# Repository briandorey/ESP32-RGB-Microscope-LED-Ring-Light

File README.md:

# ESP32 RGB Microscope LED Ring Light
ESP32 based RGB LED controller and LED ring for a microscope

The **PCB files** are in Diptrace format.

The **firmware** folder contains the firmware for the ESP32 module

The **3D Models** folder contains design files for the plastic case.

More details about this project are on my blog at [https://www.briandorey.com/post/esp32-rgb-led-microscope-ringlight](https://www.briandorey.com/post/esp32-rgb-led-microscope-ringlight)

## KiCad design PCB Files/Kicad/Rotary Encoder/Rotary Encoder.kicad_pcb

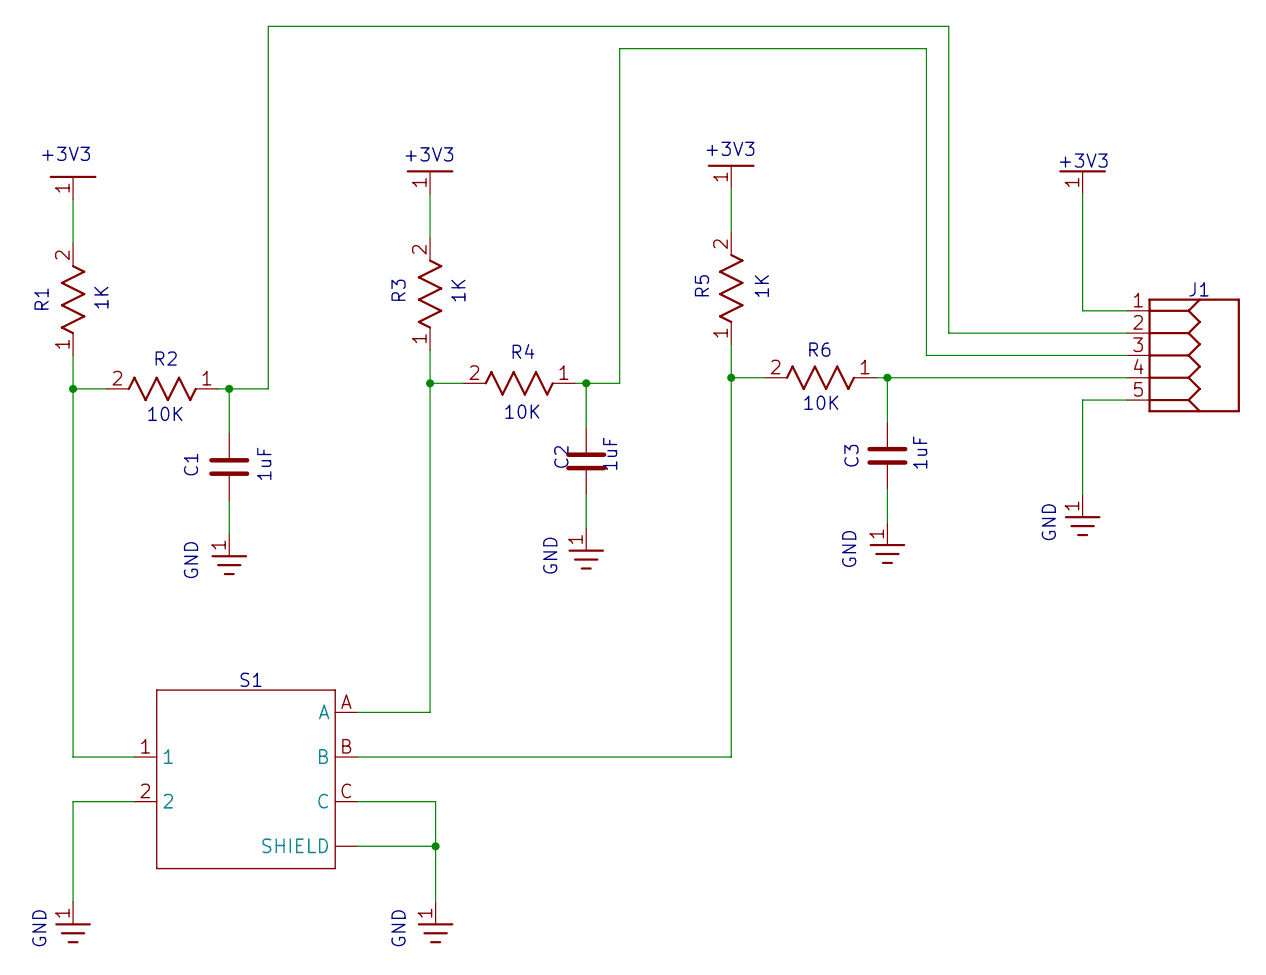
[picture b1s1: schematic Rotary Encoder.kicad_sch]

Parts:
C1, C2, C3: 1uF; CAP_0603
J1: DEV_J1; RHDRV5W80P254_5X1_1320X250H875_AP1
R1, R3, R5: 1K; RES_0603
R2, R4, R6: 10K; RES_0603
S1: 482020514001; SW_482020514001

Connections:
3V3: J1.1, R1.2, R3.2, R5.2
A: C2.1, J1.3, R4.1
B: C3.1, J1.4, R6.1
GND: C1.2, C2.2, C3.2, J1.5, S1.2, S1.C, S1.S1 (SHIELD), S1.S2 (SHIELD)
Net_1: R1.1, R2.2, S1.1
Net_5: R3.1, R4.2, S1.A
Net_7: R5.1, R6.2, S1.B
SW: C1.1, J1.2, R2.1

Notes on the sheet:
GND
+3V3
1uF
10K

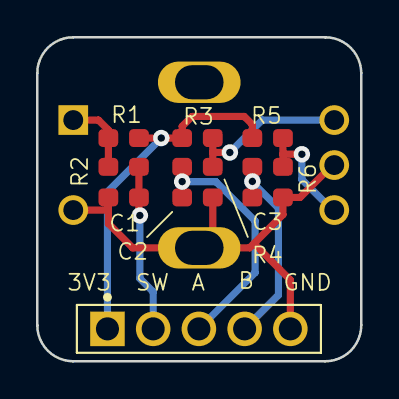
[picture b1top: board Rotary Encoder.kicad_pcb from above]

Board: 2 copper layers, 18.0 x 18.0 mm, 11 parts (1 on the bottom side), 8 nets.

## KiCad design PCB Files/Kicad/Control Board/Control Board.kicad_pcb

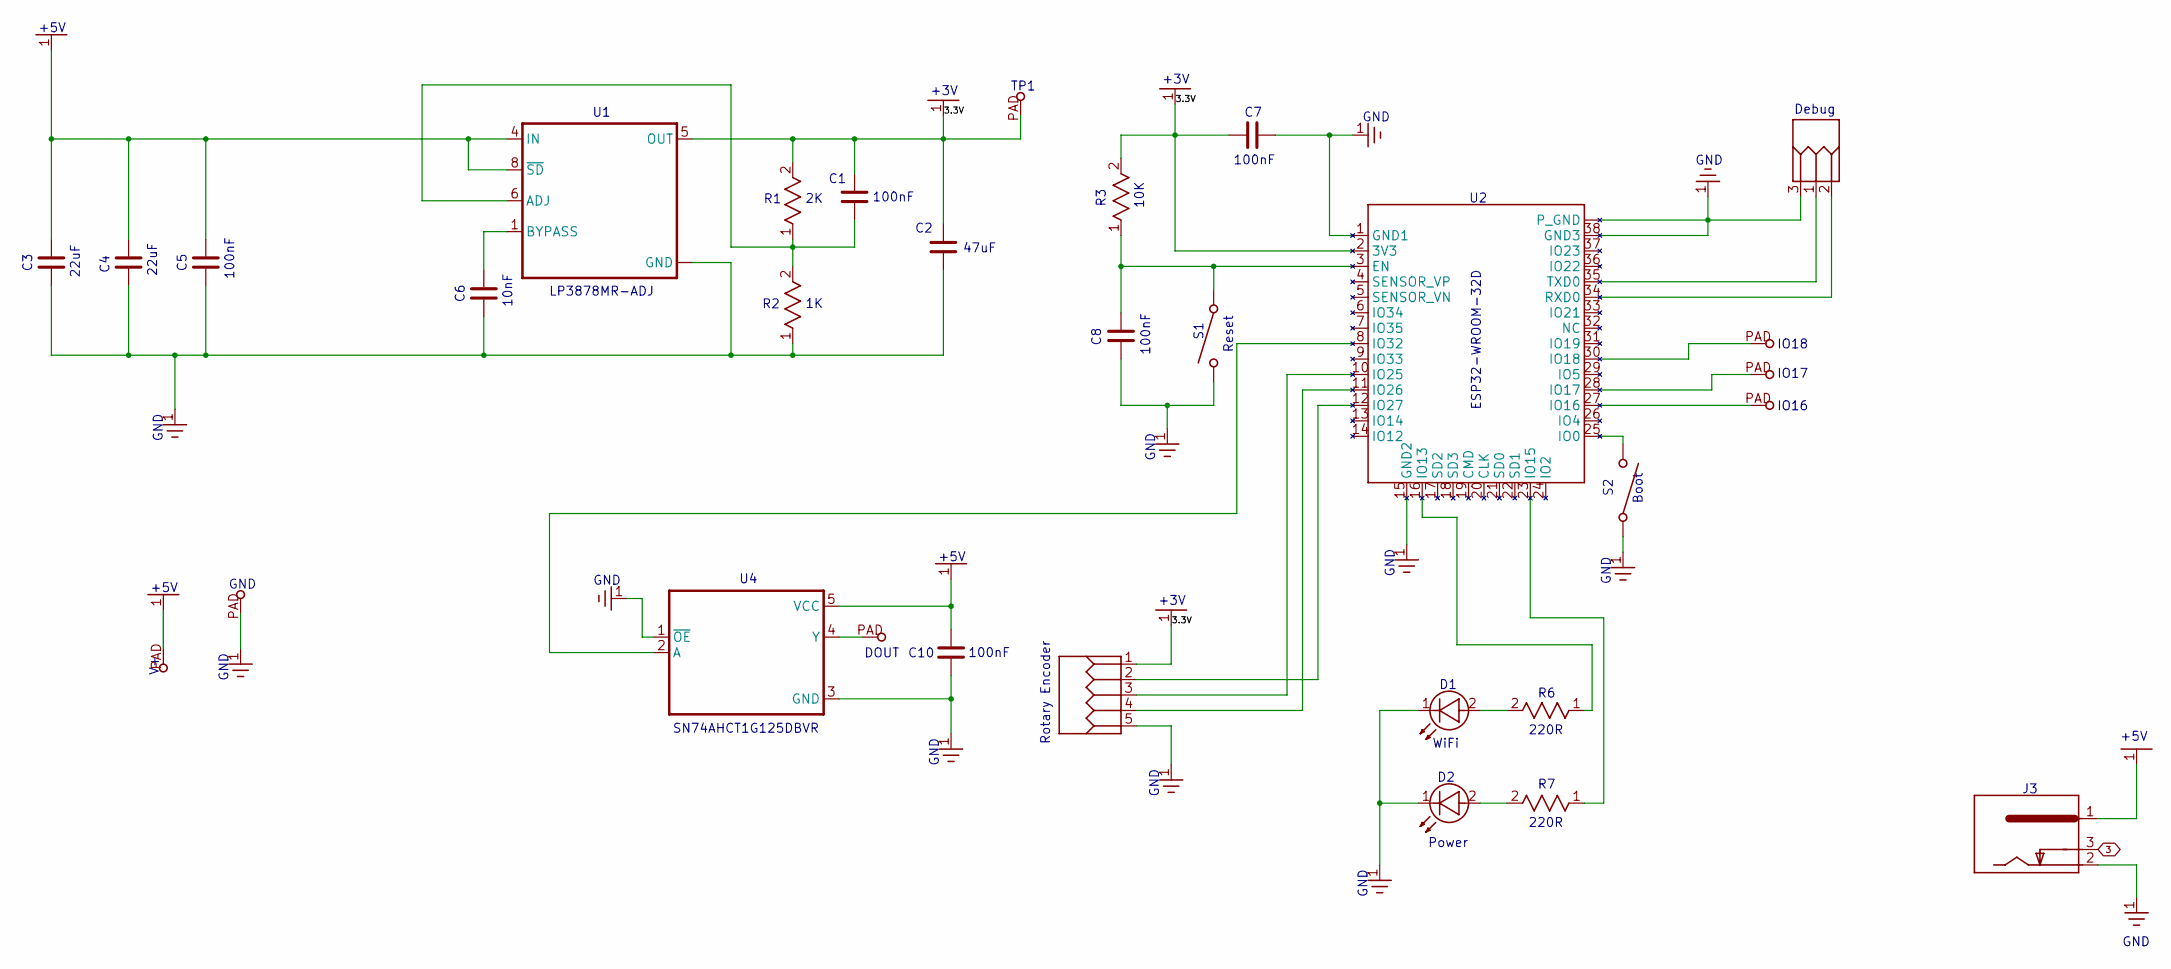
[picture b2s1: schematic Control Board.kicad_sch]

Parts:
C1, C5, C7, C8, C10: 100nF; CAP_0603_M
C2: 47uF; CAP_1210_M
C3, C4: 22uF; CAP_1210_M
C6: 10nF; CAP_0603_M
D1: WiFi; DIO_0805
D2: Power; DIO_0805
DOUT0: SMD/RREC2.0X4.0; LEAD_1.00MM
GND0: SMD/RREC2.0X4.0; LEAD_1.00MM
IO16, IO17, IO18: SMD/RREC2.0X4.0; LEAD_1.00MM
J1: DEBUG; TEST_PADS_3_PIN
J2: ROTARY_ENCODER; RHDRV5W80P254_5X1_1320X250H875_AP1
J3: 694108301002; CUI_PJ-035DH
R1: 2K; RES_0603
R2: 1K; RES_0603
R3: 10K; RES_0603
R6, R7: 220R; RES_0603_19
S1: RESET; EVQPT9A15
S2: BOOT; EVQPT9A15
TP1: 3V3; SMD_R1.3X1.3
U1: LP3878MR-ADJ; SOIC-8EP_150MIL
U2: ESP32-WROOM-32D
U4: SN74AHCT1G125DBVR; SOT95P280X145-5N
V+0: SMD/RREC2.0X4.0; LEAD_1.00MM

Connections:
3.3V: C1.1, C2.1, C7.1, J2.1, R1.2, R3.2, TP1.PAD, U1.5 (OUT), U2.2 (3V3)
5V: C3.1, C4.1, C5.1, C10.1, J3.1, U1.4 (IN), U1.8 (~SD), U4.5 (VCC), V+0.PAD
GND: C2.2, C3.2, C4.2, C5.2, C6.2, C7.2, C8.2, C10.2, D1.1 (K), D2.1 (K), GND0.PAD, J1.3 (1), J2.5, J3.2, R2.1, S1.2 (C2), S1.3 (C2), S2.1 (C1), S2.4 (C1), U1.3 (GND), U1.9 (GND), U2.1 (GND1), U2.15 (GND2), U2.38 (GND3), U2.39 (P_GND), U2.40, U2.41, U2.42 (P_GND), U2.43 (P_GND), U2.44, U2.45, U2.46, U2.47, U4.1 (~OE), U4.3 (GND); also elsewhere on the board
Net_0: U2.8 (IO32), U4.2 (A)
Net_1: R7.1 (A), U2.23 (IO15)
Net_2: J2.4, U2.11 (IO26)
Net_3: IO16.PAD, U2.27 (IO16)
Net_6: S2.2 (C2), S2.3 (C2), U2.25 (IO0)
Net_7: J2.3, U2.10 (IO25)
Net_8: C8.1, R3.1, S1.1 (C1), S1.4 (C1), U2.3 (EN)
Net_10: DOUT0.PAD, U4.4 (Y)
Net_11: R6.1 (A), U2.16 (IO13)
Net_12: J2.2, U2.12 (IO27)
Net_13: D1.2 (A), R6.2 (B)
Net_14: D2.2 (A), R7.2 (B)
Net_18: C6.1, U1.1 (BYPASS)
Net_19: C1.2, R1.1, R2.2, U1.6 (ADJ)
Net_20: IO17.PAD, U2.28 (IO17)
Net_21: IO18.PAD, U2.30 (IO18)
RX: J1.2 (3), U2.34 (RXD0)
TX: J1.1 (2), U2.35 (TXD0)

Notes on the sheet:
+5V
GND
+3V
100nF
Boot
47uF
Debug
IO17
10nF
22uF
220R
Reset
Power
10K
IO16
SN74AHCT1G125DBVR
WiFi
DOUT
LP3878MR-ADJ
Rotary Encoder
C10
IO18
TP1
ESP32-WROOM-32D

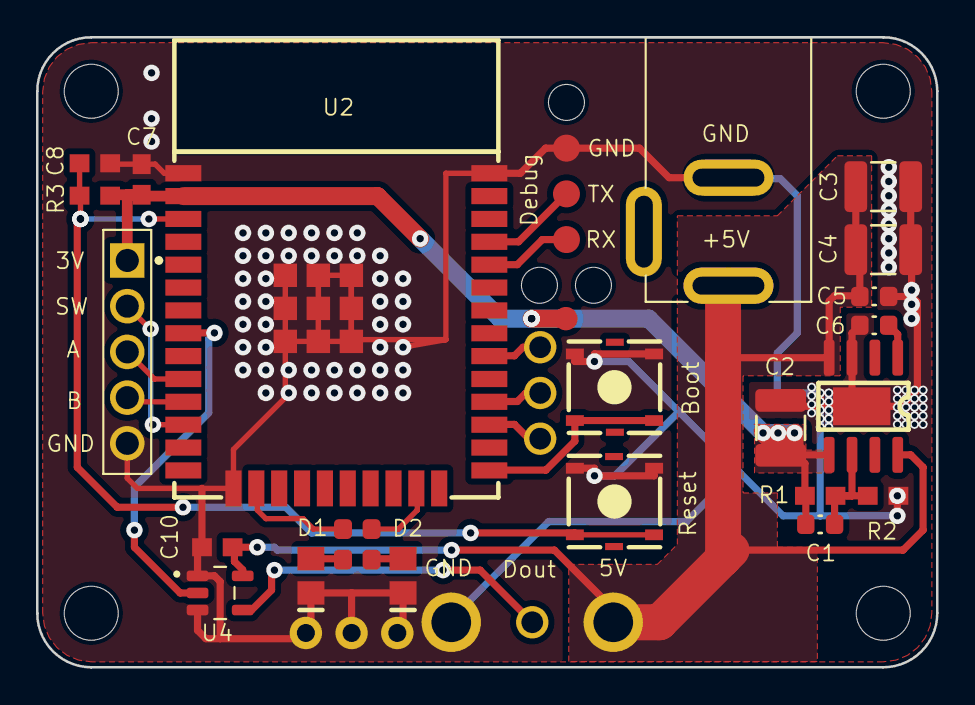
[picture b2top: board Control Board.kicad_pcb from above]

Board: 2 copper layers, 50.0 x 35.0 mm, 38 parts (0 on the bottom side), 21 nets.

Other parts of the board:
Pad1, Pad2, Pad3: PAD; Pad
UNK_HOLE_0: dummyfp0
UNK_HOLE_1: dummyfp1
UNK_HOLE_2: dummyfp2
UNK_HOLE_3: dummyfp3

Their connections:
GND: Pad1.1, Pad2.1, Pad3.1; also elsewhere on the board

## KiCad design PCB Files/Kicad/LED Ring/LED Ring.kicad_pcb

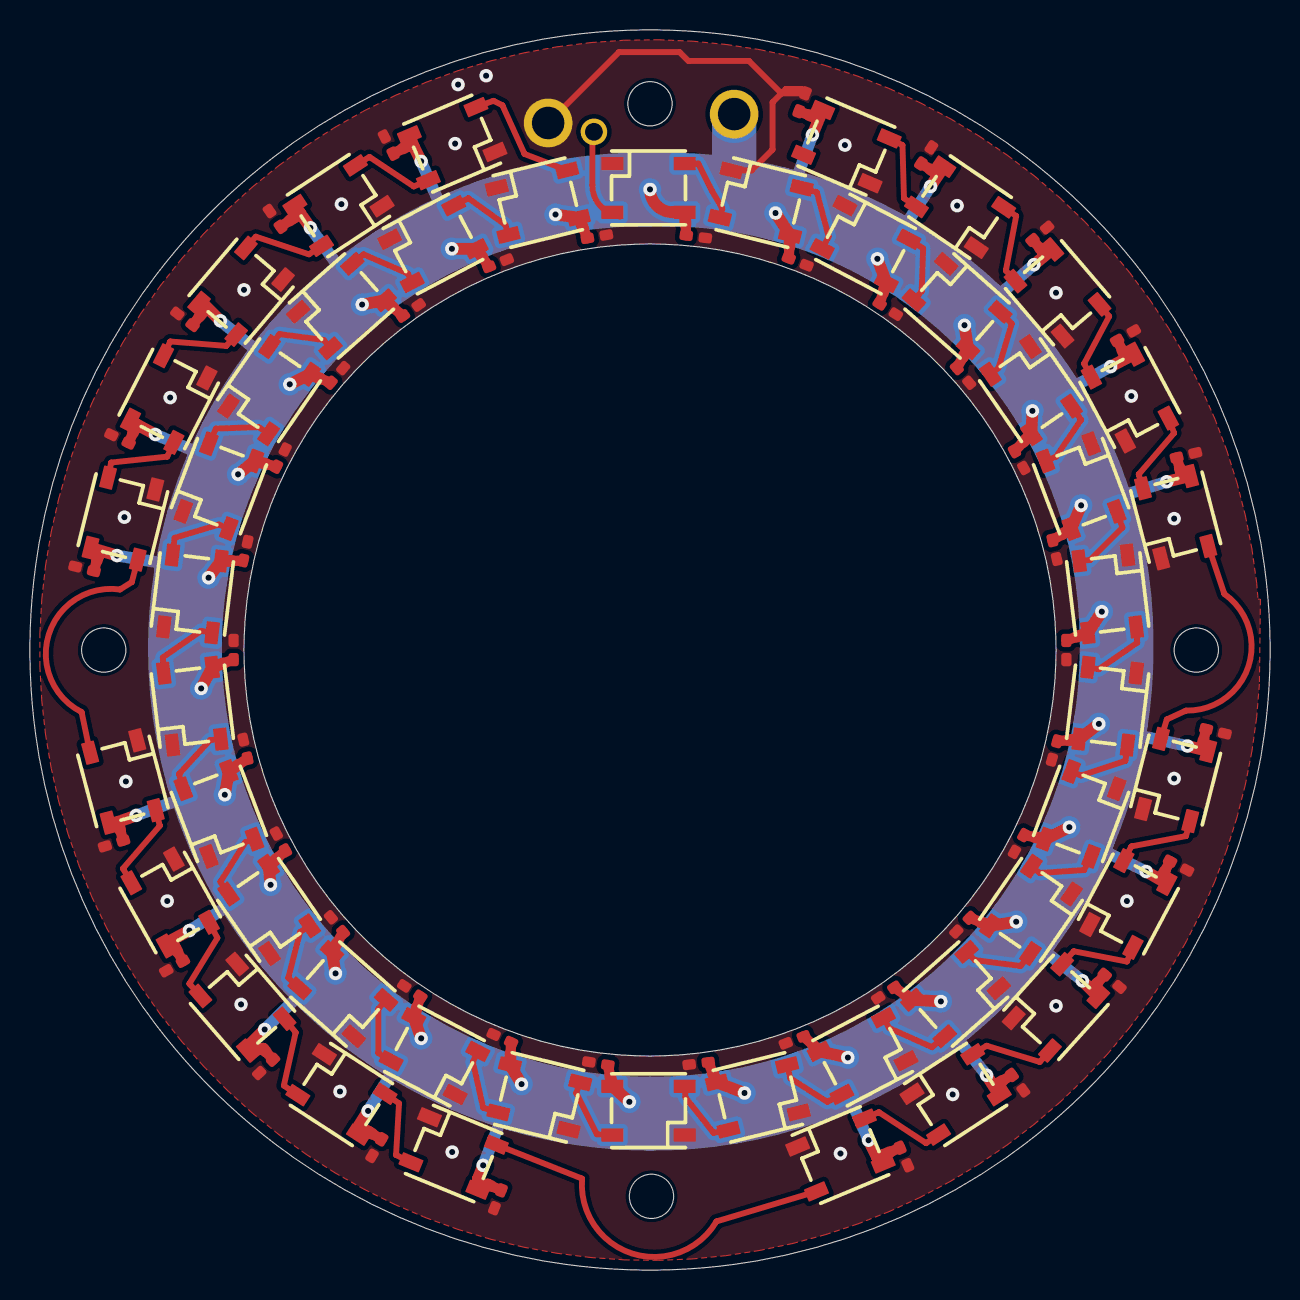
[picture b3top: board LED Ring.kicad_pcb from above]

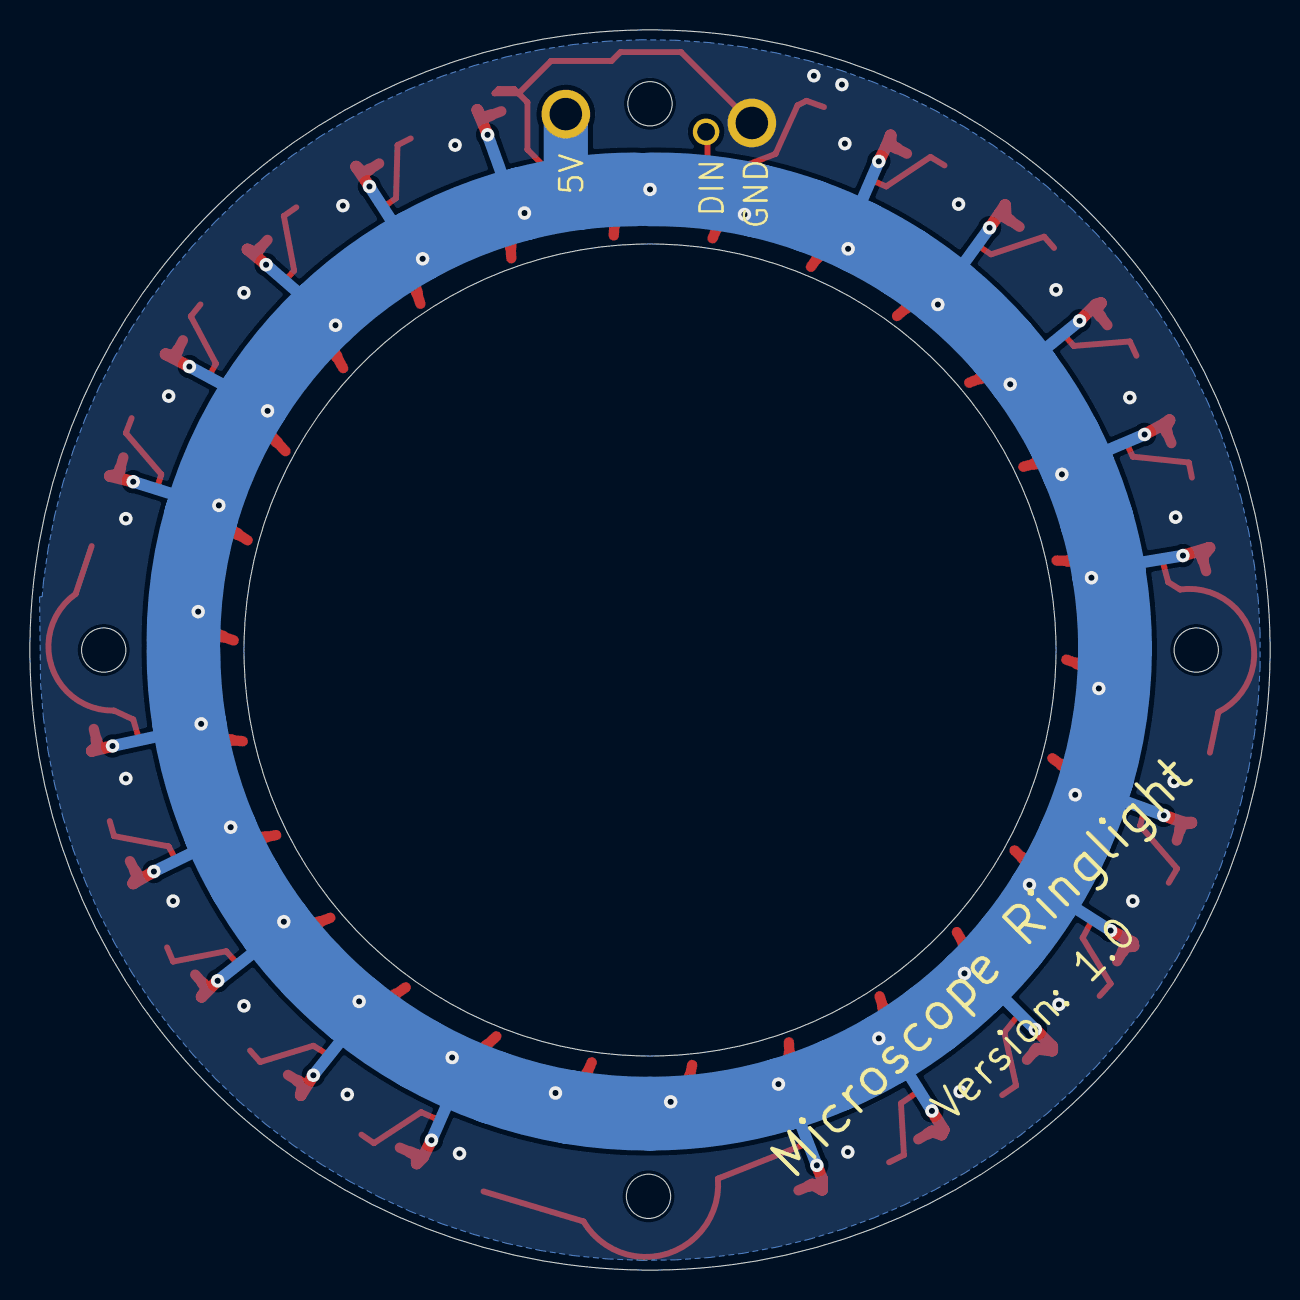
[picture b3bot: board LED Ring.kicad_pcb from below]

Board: 2 copper layers, 84.0 x 84.0 mm, 99 parts (3 on the bottom side), 48 nets.

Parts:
C1, C2, C3, C4, C5, C6, C7, C8, C9, C10, C11, C12, C13, C14, C15, C16, C17, C18, C19, C20, C21, C22, C23, C24, C25, C26, C27, C28, C29, C30, C31, C32, C33, C34, C35, C36, C37, C38, C39, C40, C41, C42, C43, C44, C45, C46: CAP_0603; CAP_0402
DIN0: SMD/RREC2.0X4.0; Lead_1.00mm
GND0: SMD/RREC2.0X4.0; Lead_2.00mm
LED1, LED2, LED3, LED4, LED5, LED6, LED7, LED8, LED9, LED10, LED11, LED12, LED13, LED14, LED15, LED16, LED17, LED18, LED19, LED20, LED21, LED22, LED23, LED24, LED25, LED26, LED27, LED28, LED29, LED30, LED31, LED32, LED33, LED34, LED35, LED36, LED37, LED38, LED39, LED40, LED41, LED42, LED43, LED44, LED45, LED46: WS2812B
UNK_HOLE_0: dummyfp0
UNK_HOLE_1: dummyfp1
UNK_HOLE_2: dummyfp2
UNK_HOLE_3: dummyfp3
V+0: SMD/RREC2.0X4.0; Lead_2.00mm

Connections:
Net_0: C1.1, C2.1, C3.1, C4.1, C5.1, C6.1, C7.1, C8.1, C9.1, C10.1, C11.1, C12.1, C13.1, C14.1, C15.1, C16.1, C17.1, C18.1, C19.1, C20.1, C21.1, C22.1, C23.1, C24.1, C25.1, C26.1, C27.1, C28.1, C29.1, C30.1, C31.1, C32.1, C33.1, C34.1, C35.1, C36.1, C37.1, C38.1, C39.1, C40.1, C41.1, C42.1, C43.1, C44.1, C45.1, C46.1, LED1.1, LED2.1, LED3.1, LED4.1, LED5.1, LED6.1, LED7.1, LED8.1, LED9.1, LED10.1, LED11.1, LED12.1, LED13.1, LED14.1, LED15.1, LED16.1, LED17.1, LED18.1, LED19.1, LED20.1, LED21.1, LED22.1, LED23.1, LED24.1, LED25.1, LED26.1, LED27.1, LED28.1, LED29.1, LED30.1, LED31.1, LED32.1, LED33.1, LED34.1, LED35.1, LED36.1, LED37.1, LED38.1, LED39.1, LED40.1, LED41.1, LED42.1, LED43.1, LED44.1, LED45.1, LED46.1, V+0.PAD
Net_1: C1.2, C2.2, C3.2, C4.2, C5.2, C6.2, C7.2, C8.2, C9.2, C10.2, C11.2, C12.2, C13.2, C14.2, C15.2, C16.2, C17.2, C18.2, C19.2, C20.2, C21.2, C22.2, C23.2, C24.2, C25.2, C26.2, C27.2, C28.2, C29.2, C30.2, C31.2, C32.2, C33.2, C34.2, C35.2, C36.2, C37.2, C38.2, C39.2, C40.2, C41.2, C42.2, C43.2, C44.2, C45.2, C46.2, GND0.PAD, LED1.3, LED2.3, LED3.3, LED4.3, LED5.3, LED6.3, LED7.3, LED8.3, LED9.3, LED10.3, LED11.3, LED12.3, LED13.3, LED14.3, LED15.3, LED16.3, LED17.3, LED18.3, LED19.3, LED20.3, LED21.3, LED22.3, LED23.3, LED24.3, LED25.3, LED26.3, LED27.3, LED28.3, LED29.3, LED30.3, LED31.3, LED32.3, LED33.3, LED34.3, LED35.3, LED36.3, LED37.3, LED38.3, LED39.3, LED40.3, LED41.3, LED42.3, LED43.3, LED44.3, LED45.3, LED46.3
Net_2: LED1.2, LED2.4
Net_3: LED2.2, LED3.4
Net_4: LED3.2, LED4.4
Net_5: LED4.2, LED5.4
Net_6: LED5.2, LED6.4
Net_7: LED6.2, LED7.4
Net_8: LED7.2, LED8.4
Net_9: LED8.2, LED9.4
Net_10: LED9.2, LED10.4
Net_11: LED19.2, LED20.4
Net_12: LED18.2, LED19.4
Net_13: LED17.2, LED18.4
Net_14: LED16.2, LED17.4
Net_15: LED15.2, LED16.4
Net_16: LED14.2, LED15.4
Net_17: LED13.2, LED14.4
Net_18: LED12.2, LED13.4
Net_19: LED11.2, LED12.4
Net_20: LED21.2, LED22.4
Net_21: LED22.2, LED23.4
Net_22: LED23.2, LED24.4
Net_23: LED24.2, LED25.4
Net_24: LED25.2, LED26.4
Net_25: LED26.2, LED27.4
Net_26: LED27.2, LED28.4
Net_27: LED28.2, LED29.4
Net_28: LED29.2, LED30.4
Net_29: LED39.2, LED40.4
Net_30: LED38.2, LED39.4
Net_31: LED37.2, LED38.4
Net_32: LED36.2, LED37.4
Net_33: LED35.2, LED36.4
Net_34: LED34.2, LED35.4
Net_35: LED33.2, LED34.4
Net_36: LED32.2, LED33.4
Net_37: LED31.2, LED32.4
Net_38: LED10.2, LED11.4
Net_39: LED20.2, LED21.4
Net_40: DIN0.PAD, LED1.4
Net_44: LED45.2, LED46.4
Net_45: LED44.2, LED45.4
Net_46: LED43.2, LED44.4
Net_47: LED42.2, LED43.4
Net_48: LED41.2, LED42.4
Net_49: LED30.2, LED31.4
Net_50: LED40.2, LED41.4

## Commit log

2024-04-13 initial upload
2025-05-16 Added kicad versions
